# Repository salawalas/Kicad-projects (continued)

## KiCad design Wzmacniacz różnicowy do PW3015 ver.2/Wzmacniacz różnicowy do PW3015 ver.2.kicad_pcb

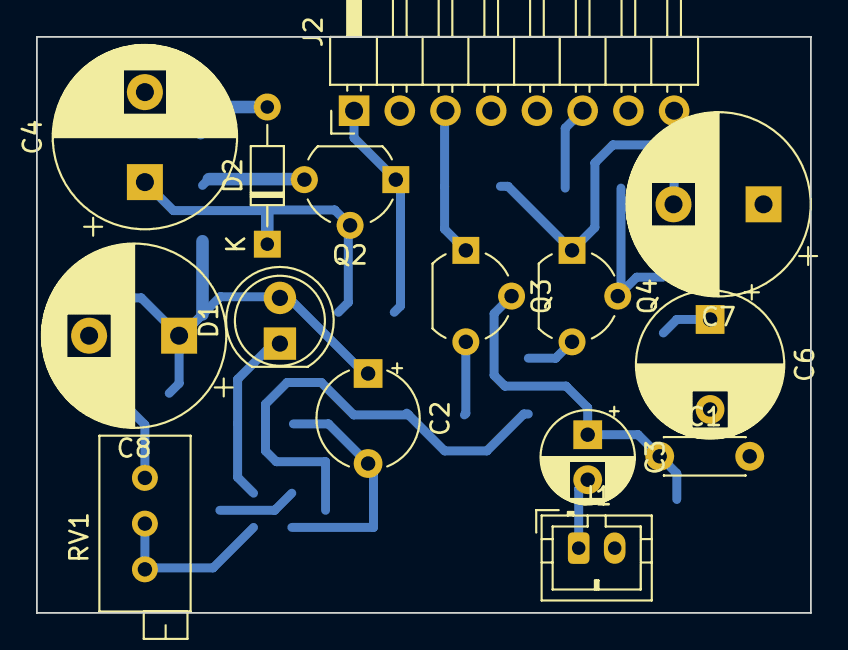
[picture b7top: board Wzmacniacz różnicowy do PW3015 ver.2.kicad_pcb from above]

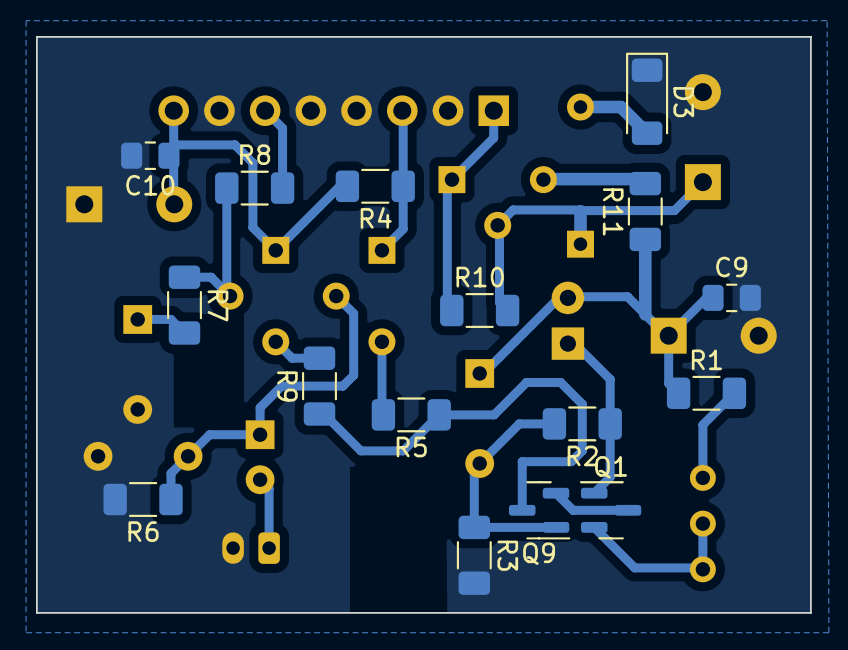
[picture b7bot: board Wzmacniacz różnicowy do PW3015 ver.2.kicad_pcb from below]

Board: 2 copper layers, 43.0 x 32.0 mm, 31 parts (16 on the bottom side), 21 nets.

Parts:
C1: 330p; C_Disc_D4.3mm_W1.9mm_P5.00mm
C2: 33u/25V; CP_Radial_Tantal_D5.5mm_P5.00mm
C3: 2u2/16V; CP_Radial_D5.0mm_P2.50mm
C4, C7, C8: 220u/35V; CP_Radial_D10.0mm_P5.00mm
C6: 47u/25V; CP_Radial_D8.0mm_P5.00mm
C9, C10: 100n; C_0805_2012Metric_Pad1.18x1.45mm_HandSolder
D1: LED_Small; LED_D5.0mm
D2: 24V; D_DO-34_SOD68_P7.62mm_Horizontal
D3: 1N4148; D_MiniMELF
J1: Conn_01x02; JST_PH_B2B-PH-K_1x02_P2.00mm_Vertical
J2: Conn_01x08; PinHeader_1x08_P2.54mm_Horizontal
Q1, Q9: BC858; SOT-23
Q2: BC237; TO-92_Wide
Q3, Q4: BC560C; TO-92_Wide
R1: 510; R_1206_3216Metric_Pad1.30x1.75mm_HandSolder
R2: 470; R_1206_3216Metric_Pad1.30x1.75mm_HandSolder
R3: 10k; R_1206_3216Metric_Pad1.30x1.75mm_HandSolder
R4, R10: 620; R_1206_3216Metric_Pad1.30x1.75mm_HandSolder
R5, R9: 220; R_1206_3216Metric_Pad1.30x1.75mm_HandSolder
R6, R8: 68k; R_1206_3216Metric_Pad1.30x1.75mm_HandSolder
R7: 1k; R_1206_3216Metric_Pad1.30x1.75mm_HandSolder
R11: 10; R_1206_3216Metric_Pad1.30x1.75mm_HandSolder
RV1: 1k; Potentiometer_Bourns_3296X_Horizontal

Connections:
GND: C1.2, C4.2, C6.2, C7.1, C8.2, C9.2, C10.2, D3.1 (K), J1.2, J2.2, J2.4, J2.5, J2.7, R3.2, R6.2
unnamed: C6.1, R7.2
unnamed: C2.1, C8.1, C9.1, D1.2 (A), R1.1, R11.1
unnamed: D1.1 (K), Q1.1 (B), R2.1
unnamed: D2.2 (A), D3.2 (A)
unnamed: C4.1, D2.1 (K), Q2.2 (B), R10.2
unnamed: C3.2, J1.1
unnamed: J2.1, Q2.1 (C), R10.1
unnamed: J2.3, Q3.1 (C), R4.1
unnamed: J2.6, R8.2
unnamed: C7.2, C10.1, J2.8, Q4.1 (C), R4.2
unnamed: Q1.3 (C), Q9.2 (E)
unnamed: Q1.2 (E), RV1.2, RV1.3
unnamed: Q2.3 (E), R11.2
unnamed: C1.1, C3.1, Q3.2 (B), R6.1
unnamed: Q3.3 (E), R5.2
unnamed: Q4.2 (B), R7.1, R8.1
unnamed: Q4.3 (E), R9.2
unnamed: C2.2, Q9.1 (B), R2.2, R3.1
unnamed: Q9.3 (C), R5.1, R9.1
unnamed: R1.2, RV1.1

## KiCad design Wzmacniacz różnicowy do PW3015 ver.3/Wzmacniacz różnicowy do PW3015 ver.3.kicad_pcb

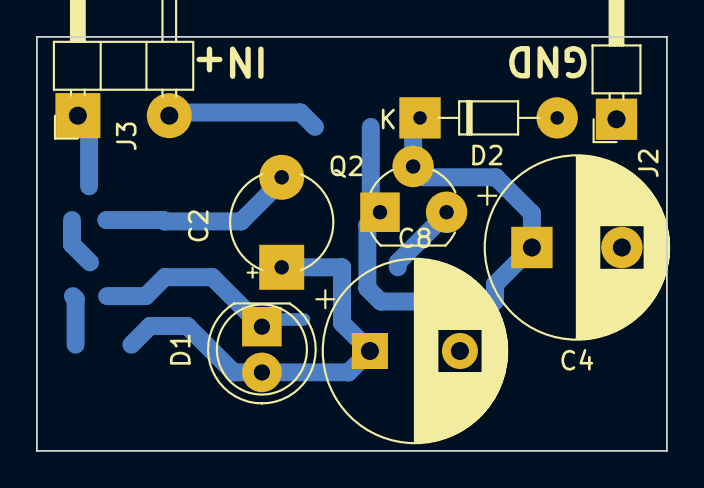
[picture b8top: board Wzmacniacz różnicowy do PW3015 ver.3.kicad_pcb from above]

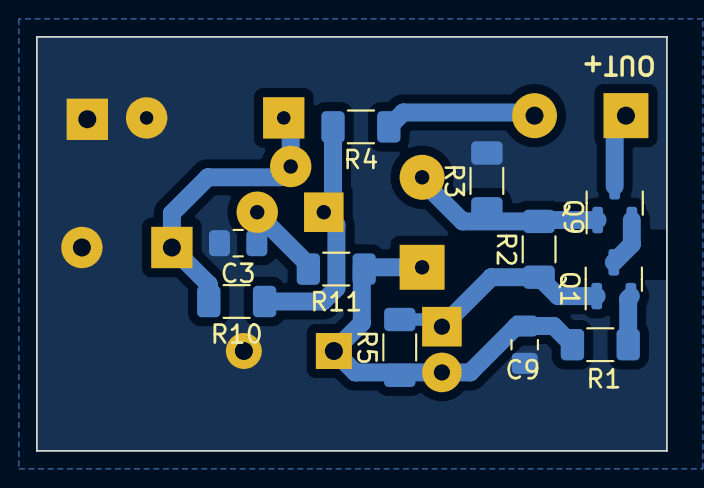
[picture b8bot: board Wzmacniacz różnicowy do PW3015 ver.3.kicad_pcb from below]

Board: 2 copper layers, 35.0 x 23.0 mm, 19 parts (11 on the bottom side), 11 nets.

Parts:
C2: 33u/25V; CP_Radial_Tantal_D5.5mm_P5.00mm
C3, C9: 100n; C_0805_2012Metric_Pad1.18x1.45mm_HandSolder
C4: 220u/16V; CP_Radial_D10.0mm_P5.00mm
C8: 470u/16V; CP_Radial_D10.0mm_P5.00mm
D1: LED_Small; LED_D5.0mm
D2: 16V; D_DO-34_SOD68_P7.62mm_Horizontal
J2: Conn_01x01_Pin; PinHeader_1x01_P2.54mm_Horizontal
J3: Conn_01x03_Pin; PinHeader_1x03_P2.54mm_Horizontal
Q1, Q9: BC858; SOT-23
Q2: BC238; TO-92_Wide
R1: 200; R_1206_3216Metric_Pad1.30x1.75mm_HandSolder
R2: 470; R_1206_3216Metric_Pad1.30x1.75mm_HandSolder
R3: 4k3; R_1206_3216Metric_Pad1.30x1.75mm_HandSolder
R4: 560; R_1206_3216Metric_Pad1.30x1.75mm_HandSolder
R5: 100k; R_1206_3216Metric_Pad1.30x1.75mm_HandSolder
R10: 2k2; R_1206_3216Metric_Pad1.30x1.75mm_HandSolder
R11: 10; R_1206_3216Metric_Pad1.30x1.75mm_HandSolder

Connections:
+38V: J3.3, R4.1
GND: C3.2, C4.2, C8.2, C9.2, D2.2 (A), J2.1, R3.2
unnamed: C2.1, C8.1, C9.1, D1.2 (A), R1.1, R5.1, R11.1
unnamed: D1.1 (K), Q1.1 (B), R2.1, R5.2
unnamed: C4.1, D2.1 (K), Q2.2 (B), R10.2
unnamed: J3.1, Q9.3 (C)
unnamed: Q1.3 (C), Q9.2 (E)
unnamed: Q1.2 (E), R1.2
unnamed: Q2.1 (C), R4.2, R10.1
unnamed: C3.1, Q2.3 (E), R11.2
unnamed: C2.2, Q9.1 (B), R2.2, R3.1
